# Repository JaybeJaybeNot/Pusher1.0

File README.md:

<p align="center"><i>June 8, 2026</i></p>

**Affiliation:** Fallout, Hackclub

Sanity Checked by a friend, a CS Graduate from UofM working in robotics.

Pusher is a **4 Degree of Freedom wearable robotic arm** based on the anatomical structure of the human arm, with a maximum reach of approximately **0.65 meters** and a weight of **5 kilograms**. It is designed for **modularity**, aiming to serve as an affordable, general-purpose **research platform** for Human-Computer Interfacing, such as studies involving **EMG, EEG, and Computer Vision**, to assist in the **control of supernumerary arms**. As such, this project is intended for both undergraduate researchers and hobbyists looking for an introduction to the study of HCI robotics, with potential to be used in graduate-school prototyping due to the ease of production and low cost.

***Why I Started This Project***

On the surface level, the this project may seem to simply be a project aiming to develop a supernumerary, robotic arm to assist in human tasks. However, due to the modularity and inexpensiveness of the project, it serves as an amazing platform to prototype with robot theory, from inverse kinematics to computer vision, EEG/EMG signal processing, path planning, control algorithms, etc. without burning cash on hardware. In short, due to my background as an underfunded hardware researcher, I've made the "project to enable future projects"

<h1 align="center"><u>Table of Contents</u></h1>

1. [Bill of Materials](#bill-of-materials)
2. [System Diagram](#system-diagram)
3. [Building the Project](#building-the-project)
   1. [Prerequisites](#prerequisites)
   2. [Assembling Mechanical Design](#assembling-mechanical-design)
   3. [Assembling Electrical Design](#assembling-electrical-design)
   4. [Flashing Firmware](#flashing-firmware)
4. [Author's Notes](#authors-notes)
   1. [Commentary on BOM](#commentary-on-bom)
   2. [Guide to Adding Implementations (Taking Advantage of Modularity)](#guide-to-adding-implementations-taking-advantage-of-modularity)
   3. [Future Implementations by Author](#future-implementations-by-author)

<h1 align="center"><u>Bill of Materials</u></h1>

### Electronics

| Index | LCSC # | Quantity | Value | Link |
|---|---:|---:|---:|---|
| 1 | C146170 | 2 | 1.81 | [LCSC](https://www.lcsc.com/product-detail/C146170.html) |
| 2 | C22396880 | 6 | 10.34 | [LCSC](https://www.lcsc.com/product-detail/C22396880.html) |
| 3 | C49678 | 100 | 0.84 | [LCSC](https://www.lcsc.com/product-detail/C49678.html) |
| 4 | C72487 | 20 | 0.57 | [LCSC](https://www.lcsc.com/product-detail/C72487.html) |
| 5 | C24123 | 20 | 0.30 | [LCSC](https://www.lcsc.com/product-detail/C24123.html) |
| 6 | C3869051 | 20 | 0.57 | [LCSC](https://www.lcsc.com/product-detail/C3869051.html) |
| 7 | C8465 | 5 | 0.67 | [LCSC](https://www.lcsc.com/product-detail/C8465.html) |
| 8 | C72334 | 5 | 1.01 | [LCSC](https://www.lcsc.com/product-detail/C72334.html) |
| 9 | C86513 | 4 | 6.79 | [LCSC](https://www.lcsc.com/product-detail/C86513.html) |
| 10 | C114548 | 100 | 0.36 | [LCSC](https://www.lcsc.com/product-detail/C114548.html) |
| 11 | C2930231 | 100 | 0.19 | [LCSC](https://www.lcsc.com/product-detail/C2930231.html) |
| 12 | C90964 | 5 | 3.70 | [LCSC](https://www.lcsc.com/product-detail/C90964.html) |
| 13 | C58159 | 1 | 0.38 | [LCSC](https://www.lcsc.com/product-detail/C58159.html) |
| 14 | C7467397 | 50 | 0.65 | [LCSC](https://www.lcsc.com/product-detail/C7467397.html) |
| 15 | C2930266 | 100 | 0.19 | [LCSC](https://www.lcsc.com/product-detail/C2930266.html) |
| 16 | C2907315 | 100 | 0.22 | [LCSC](https://www.lcsc.com/product-detail/C2907315.html) |
|  |  | **Total** | **28.59** |  |

### Mechanical

| Part name | Quantity | Value | Link |
|---|---:|---:|---|
| PLA Filament | 1 | 7.36 | [AliExpress](https://www.aliexpress.us/item/3256806054300015.html?spm=a2g0o.productlist.main.3.6f78379d5OwR1X&algo_pvid=498c2f52-b8c2-4add-bea6-f9bda40c924e&algo_exp_id=498c2f52-b8c2-4add-bea6-f9bda40c924e-2&pdp_ext_f=%7B%22order%22%3A%22488%22%2C%22eval%22%3A%221%22%2C%22fromPage%22%3A%22search%22%7D&pdp_npi=6%40dis%21USD%2122.79%217.36%21%21%2122.79%217.36%21%402140c1c317807875296987000e9684%2112000058209259440%21sea%21US%210%21ABX%211%210%21n_tag%3A-29910%3Bd%3Ae1bbef76%3Bm03_new_user%3A-29895%3BpisId%3A5000000208023469&curPageLogUid=Qx4M7j8exyPx&utparam-url=scene%3Asearch%7Cquery_from%3A%7Cx_object_id%3A1005006240614767%7C_p_origin_prod%3A) |
| motors | 4 | 30 | [Precision Mini Drives](https://precisionminidrives.com/product/shaft-diameter-8mm-10mm-micro-dc-gear-motor-model-nfp-42-775-ce-12v-24v?attribute_option=12V%2C+80RPM&attribute_shaft-diameter=10mm&utm_source=GoogleAds&utm_campaign=PMax&utm_medium=Google%20Shopping&utm_term=adtribes&utm_content=%7Bproduct_id%7D&gad_source=1&gad_campaignid=18478080173&gbraid=0AAAAAomY7RXK-6ddvY5v_P-wvX2-wvXLt&gclid=CjwKCAjw5NvPBhAoEiwA_2egfvITADIqACLw4gyQt7JJ5pv2qg0MlFNwTrXCpuVo1aJEWzca6XUyrBoCjcwQAvD_BwE) |
| RU-28 | 4 | 19.91 | [AliExpress](https://www.aliexpress.us/item/3256809392312866.html?src=google&src=google&albch=shopping&acnt=708-803-3821&isdl=y&slnk=&plac=&mtctp=&albbt=Google_7_shopping&aff_platform=google&aff_short_key=UneMJZVf&gclsrc=aw.ds&albagn=888888&ds_e_adid=&ds_e_matchtype=&ds_e_device=c&ds_e_network=x&ds_e_product_group_id=&ds_e_product_id=en3256809392312866&ds_e_product_merchant_id=107675220&ds_e_product_country=US&ds_e_product_language=en&ds_e_product_channel=online&ds_e_product_store_id=&ds_url_v=2&albcp=20123152476&albag=&isSmbAutoCall=false&needSmbHouyi=false&gad_source=1&gad_campaignid=20127768206&gbraid=0AAAAAD6I-hH5MzbM-Qht5WI26YJI1jQ7x&gclid=CjwKCAjw5NvPBhAoEiwA_2egfknGl0bGc7tc0ydw4pmODKzmqiRzPcj2s5EQ8m0HpaPSL7tY9xceahoCLmEQAvD_BwE&gatewayAdapt=glo2usa) |
| M5 Screws (x50) | 1 | 15 | [Amazon Japan](https://www.amazon.co.jp/-/en/Button-Socket-Screws-Finish-BHSSM5X10B-50-SL/dp/B07DZN3FP5) |
| M3 screws and nuts (x20) | 1 | 9 | [Amazon Japan](https://www.amazon.co.jp/-/en/Phillips-Machine-Washers-Plastic-Countersunk/dp/B0B9YGNKV6) |
| m5 nuts (x50) | 1 | 13 | [Amazon Japan](https://www.amazon.co.jp/-/en/Thin-Nuts-Stainless-Steel-Flat/dp/B0CQ55XWQX?th=1) |
|  |  | **Total** | **244** |

**Total project cost:** **272.59**

<h1 align="center"><u>System Diagram</u></h1>

<h1 align="center"><u>Building the Project</u></h1>

## Prerequisites

what you will need:

- A 3d printer such as Bambu Lab capable of a printing area of 
- VS Code (my goat!)
- STM32CubeIDE 
- If you have v2.0 and later versions of STM32CubeIDE, you’ll also need STM32CubeMX
- ESP32 IDF
- Cura 
- an STM32 Nucleo Board
- Soldering:

Soldering:

- Soldering iron 
- Brass wool (sponges is useable, but not recommended) 
- Flux 
- Soldering gun 
- Fume extractor 
- Solder wick (recommended to remove excess solder) 

## Assembling Mechanical Design

For assembly, please see the `FINAL ASSEMBLY` file in the `mechanical design` folder, opened in CAD software such as Fusion 360.

The material modeled for stress testing and manufacturability is PLA plastic, intended for 3D printers such as the Bambu models.

In a slicer such as Cura, print the following:

- 1x `Bicep_And_Cap`
- 1x `Bicep_RU_28_Connector` (in `Bicep_And_Cap`)
- 1x `Forearm`
- 3x `Joint_Cover`
- 1x `Joint1`
- 2x `Joints_2_and_3`
- 3x `RU_28_Connector`

Approximately ~2 kg in PLA.

To assemble the physical design, it is recommended to have 30x M5 screws (10 mm) and 30x matching nuts. Then, use 15x M3 screws (10 mm) with 15x matching nuts.

## Assembling Electrical Design

Trusted vendors such as [JLCPCB](https://jlcpcb.com/) and [LCSC](https://www.lcsc.com/).

After ordering your PCB and components from JLCPCB and LCSC, hand-solder them as follows:

- 4x motor driver PCBs

- 1x main controller PCB

Motor driver PCBs are secured in a dedicated mount, 

which is fastened to the joints themselves.

The controller PCB is left separate from the rest of the arm. The recommended option is to keep it on a desk during assembly and strap it to the arm during operation.

The wiring diagram is as follows:

- Red — 24 V and 3.3 V power supply bus
- Yellow — I2C communication bus

Connections:

- From Joint 1 to Joint 2\

- From Joint 2 to Joint 3

- From Joint 3 to Bicep

The firmware includes a 360-degree clamp to prevent wires from excessive twisting and strain.

## Flashing Firmware

### Flashing STM32F103C8T6
Note: The firmware should all be in the “Brushed_DC_Motor_Controller_STM32” folder (this is the folder you select for “create project from existing stm32cubeide project”). But for additional documentation, the pinouts and clock configuration is provided below:

In STM32cubeMX, configure the pins as follows:

Now, in the Clock tab, configure the clocks as follows:

Note: The firmware should be placed in the `Brushed_DC_Motor_Controller_STM32` folder. This is the folder you select when creating a project from an existing STM32CubeIDE project.

Step 1: Connect the SWDIO, SWCLK, GND, and 3v3 on the Motor Driver stm32 with the corresponding pins on your ST-LINK. Preferably, any STM32Nucleo can be used in order to avoid third party flashers that do not work. (trust me, speaking from experience). 

(Remove the “ST-Link isolation jumpers” on CN2 on the Nucleo Board so that you’re programming the dc motor driver, not the Nucleo itself)

Step 2: Import “Brushed_DC_Motor_Controller_STM32” as an “Existing STM32 project” into stm32cubeIDE. 

Step 3: Open the project, and find the build tool on the top toolbar, then click on it: 

Verify that there are no errors. Most build errors arise from workspace configuration. If that happens, close STM32CubeIDE first. Then, reopen. When it asks for a workspace, select the “Software” folder. It should create the corresponding metadata files. Confirm that files are there. 

Step 4: Click on “debug” tool. 

Step 5: Click on “Run”:

If flashing succeeds, STM32CubeIDE should display a successful download message in the console.

### Flashing ESP32

1. Follow the steps in the AKP's IoT Tech video to download and set up ESP32 IDF. Stop around 4:20, after creating a project folder.

YouTube video: https://www.youtube.com/watch?v=xQ-Zk0FaK-c

2. At 4:20, replace the code in `hello_world_main.c` with the contents of `main.c` located in the `ESP32 Joystick Controller` folder.
3. The code does not use external libraries, so no additional imports are needed.
4. In the ESP32-IDF terminal, type:

```bash
idf.py set-target esp32
idf.py build
```

5. Connect the ESP32 to your computer via USB.

On Windows, select the ESP32 model and the communication port. Ports usually appear as `COMx`.

Then run:

```bash
idf.py -p COM3 flash
```

Replace `3` in `COM3` with the corresponding COM number.

#### Mac

On Mac, ports usually appear as `/dev/ttyUSBx`.

You can identify the port with:

```bash
ls -la /dev | grep -E "cu\.(SLAB|usbserial)"
```

Then follow these steps:

```bash
source ~/esp/esp-idf/export.sh
idf.py set-target esp32
idf.py -p /dev/cu.SLAB_USBtoUART flash
```

#### Linux

On Linux, ports usually appear as `/dev/ttyACMx`.

First, add your user to the hardware access group:

Ubuntu/Debian:

```bash
sudo usermod -aG dialout $USER
```

Arch Linux:

```bash
sudo usermod -aG uucp $USER
```

Then, find the device path with:

```bash
ls /dev/ttyUSB* /dev/ttyACM*
```

Then navigate into your project directory and select the model:

```bash
idf.py set-target esp32
```

Finally, flash and monitor:

```bash
idf.py -p /dev/ttyUSB0 flash monitor
```

Replace `/dev/ttyUSB0` with the actual device path identified above.

<h1 align="center"><u>Author's Notes</u></h1>

## Commentary on BOM

## Guide to Adding Implementations (Taking Advantage of Modularity)

## Future Implementations by Author

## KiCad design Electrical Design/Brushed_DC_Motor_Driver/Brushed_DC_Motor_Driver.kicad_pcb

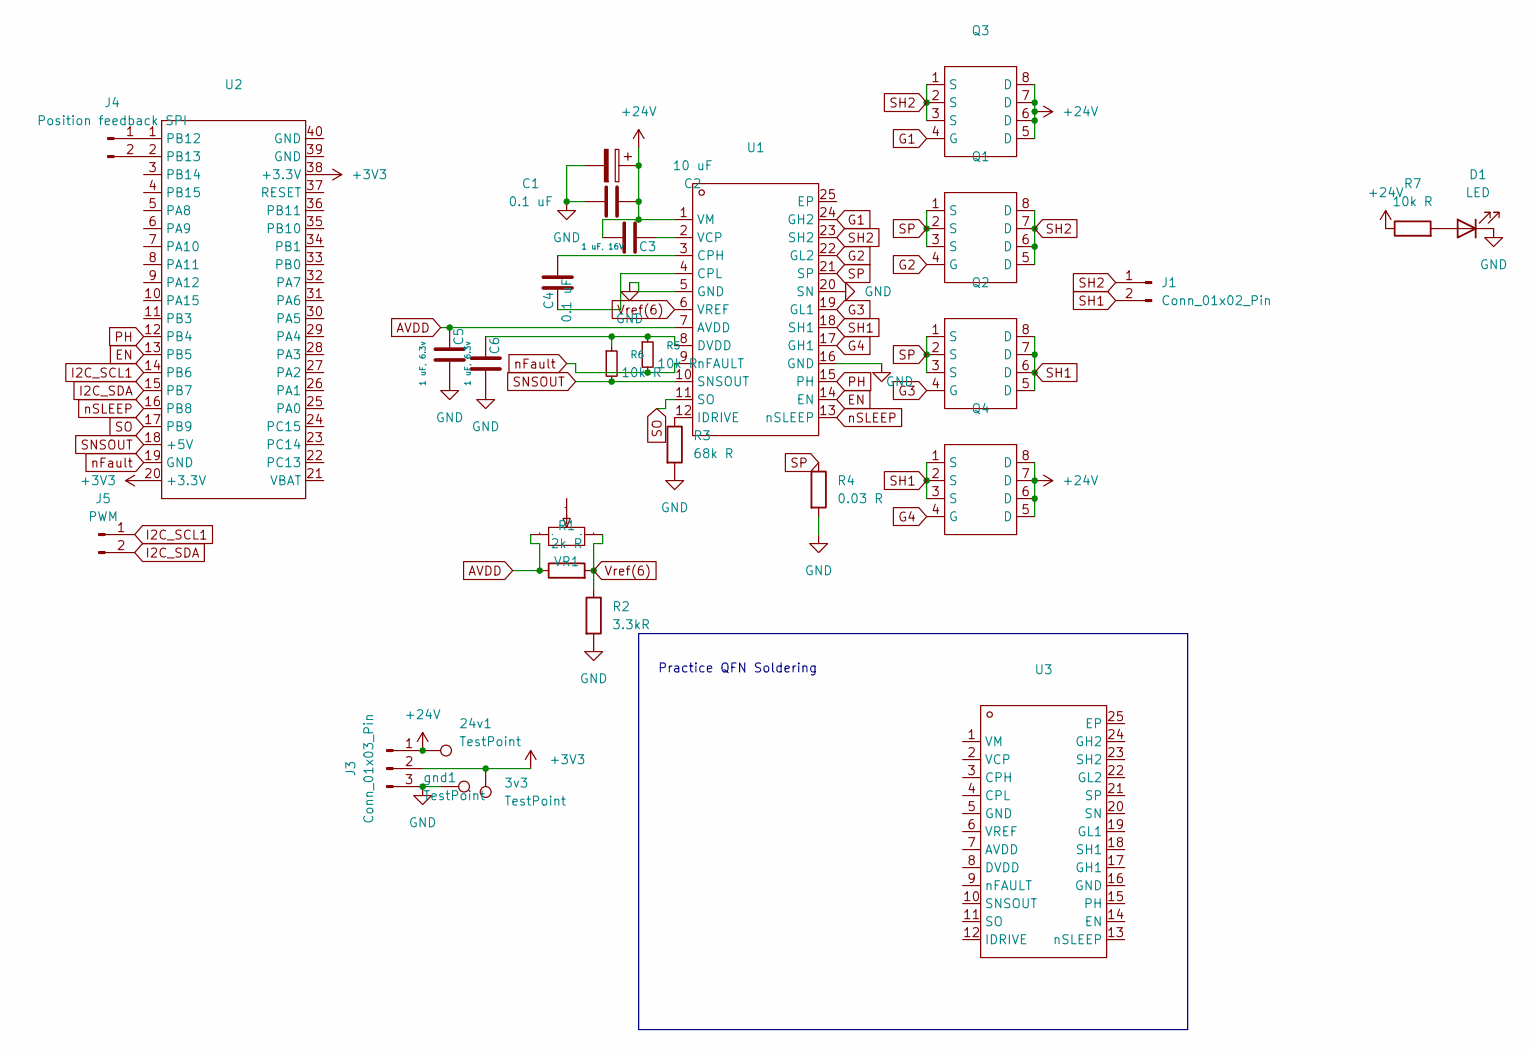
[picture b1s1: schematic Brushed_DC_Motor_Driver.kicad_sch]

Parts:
3v3, 24v1: TestPoint; TestPoint_Loop_D2.50mm_Drill1.0mm_LowProfile
C1, C4: 0.1 uF; C_0805_2012Metric_Pad1.18x1.45mm_HandSolder
C2: 10 uF; CP_Elec_5x5.4
C3: 1 uF, 16V; C_0805_2012Metric_Pad1.18x1.45mm_HandSolder
C5, C6: 1 uF, 6.3v; C_0805_2012Metric_Pad1.18x1.45mm_HandSolder
D1: LED; C_1206_3216Metric_Pad1.33x1.80mm_HandSolder
J1: Conn_01x02_Pin; Samtec_HPM-02-01-x-S_Straight_1x02_Pitch5.08mm
J3: Conn_01x03_Pin; Samtec_HPM-03-01-x-S_Straight_1x03_Pitch5.08mm
J4: Position feedback SPI; Samtec_HPM-02-01-x-S_Straight_1x02_Pitch5.08mm
J5: PWM; Samtec_HPM-02-01-x-S_Straight_1x02_Pitch5.08mm
Q1, Q2, Q3, Q4: VSON-CLIP-8_L5.0-W6.0-P1.27-BL; Manufacturer Part CSD18540Q5B; LCSC Part Name 1个N沟道 耐压:60V
R1: 2k R; C_0805_2012Metric_Pad1.18x1.45mm_HandSolder
R2: 3.3kR; C_0805_2012Metric_Pad1.18x1.45mm_HandSolder
R3: 68k R; C_0805_2012Metric_Pad1.18x1.45mm_HandSolder
R4: 0.03 R; C_0805_2012Metric_Pad1.18x1.45mm_HandSolder
R5, R6, R7: 10k R; C_0805_2012Metric_Pad1.18x1.45mm_HandSolder
U1, U3: VQFN-24_L4.0-W4.0-P0.50-BL-EP2.5; Manufacturer Part DRV8701ERGER; LCSC Part Name 有刷直流电机驱动芯片 45V
U2: CONN-TH_L53.3-W22.9_STM32F103C8T6-CARD; Manufacturer Part LCKFB-DKX-STM32F103C8T6; LCSC Part Name 立创·地阔星-STM32F103C8T6开发板
VR1: 10kΩ; RES-ADJ-TH_3362P; Manufacturer Part 3362P-1-103LF; LCSC Part Name 10kΩ ±10%
gnd1: TestPoint; TestPoint_Loop_D2.50mm_Drill1.0mm_LowProfile

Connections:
+3V3: 3v3.1, J3.2, U2.20 (+3.3V), U2.38 (+3.3V)
+24V: 24v1.1, C1.2, C2.1, C3.1, J3.1, Q3.5 (D), Q3.6 (D), Q3.7 (D), Q3.8 (D), Q4.5 (D), Q4.6 (D), Q4.7 (D), Q4.8 (D), R7.1, U1.1 (VM); also elsewhere on the board
AVDD: C5.2, R1.1, U1.7 (AVDD), VR1.3; also elsewhere on the board
EN: U1.14 (EN), U2.13 (PB5); also elsewhere on the board
G1: Q3.4 (G), U1.24 (GH2); also elsewhere on the board
G2: Q1.4 (G), U1.22 (GL2); also elsewhere on the board
G3: Q2.4 (G), U1.19 (GL1); also elsewhere on the board
G4: Q4.4 (G), U1.17 (GH1); also elsewhere on the board
GND: C1.1, C2.2, C5.1, C6.1, D1.1 (K), J3.3, R2.2, R3.2, R4.2, U1.5 (GND), U1.16 (GND), U1.20 (SN), gnd1.1; also elsewhere on the board
I2C_SCL1: J5.1, U2.14 (PB6)
I2C_SDA: J5.2, U2.15 (PB7)
unnamed: D1.2 (A), R7.2
unnamed: J4.1, U2.1 (PB12)
unnamed: J4.2, U2.2 (PB13)
unnamed 14: C4.2, U1.3 (CPH); also elsewhere on the board
unnamed 15: C4.1, U1.4 (CPL); also elsewhere on the board
unnamed 16: C6.2, R5.1, R6.1, U1.8 (DVDD); also elsewhere on the board
unnamed 17: R3.1, U1.12 (IDRIVE); also elsewhere on the board
unnamed 18: C3.2, U1.2 (VCP); also elsewhere on the board
PH: U1.15 (PH), U2.12 (PB4); also elsewhere on the board
SH1: J1.2, Q2.5 (D), Q2.6 (D), Q2.7 (D), Q2.8 (D), Q4.1 (S), Q4.2 (S), Q4.3 (S), U1.18 (SH1); also elsewhere on the board
SH2: J1.1, Q1.5 (D), Q1.6 (D), Q1.7 (D), Q1.8 (D), Q3.1 (S), Q3.2 (S), Q3.3 (S), U1.23 (SH2); also elsewhere on the board
SNSOUT: R6.2, U1.10 (SNSOUT), U2.18 (+5V); also elsewhere on the board
SO: U1.11 (SO), U2.17 (PB9); also elsewhere on the board
SP: Q1.1 (S), Q1.2 (S), Q1.3 (S), Q2.1 (S), Q2.2 (S), Q2.3 (S), R4.1, U1.21 (SP); also elsewhere on the board
Vref(6): R1.2, R2.1, U1.6 (VREF), VR1.1; also elsewhere on the board
nFault: R5.2, U1.9 (nFAULT), U2.19 (GND); also elsewhere on the board
nSLEEP: U1.13 (nSLEEP), U2.16 (PB8); also elsewhere on the board

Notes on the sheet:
Practice QFN Soldering

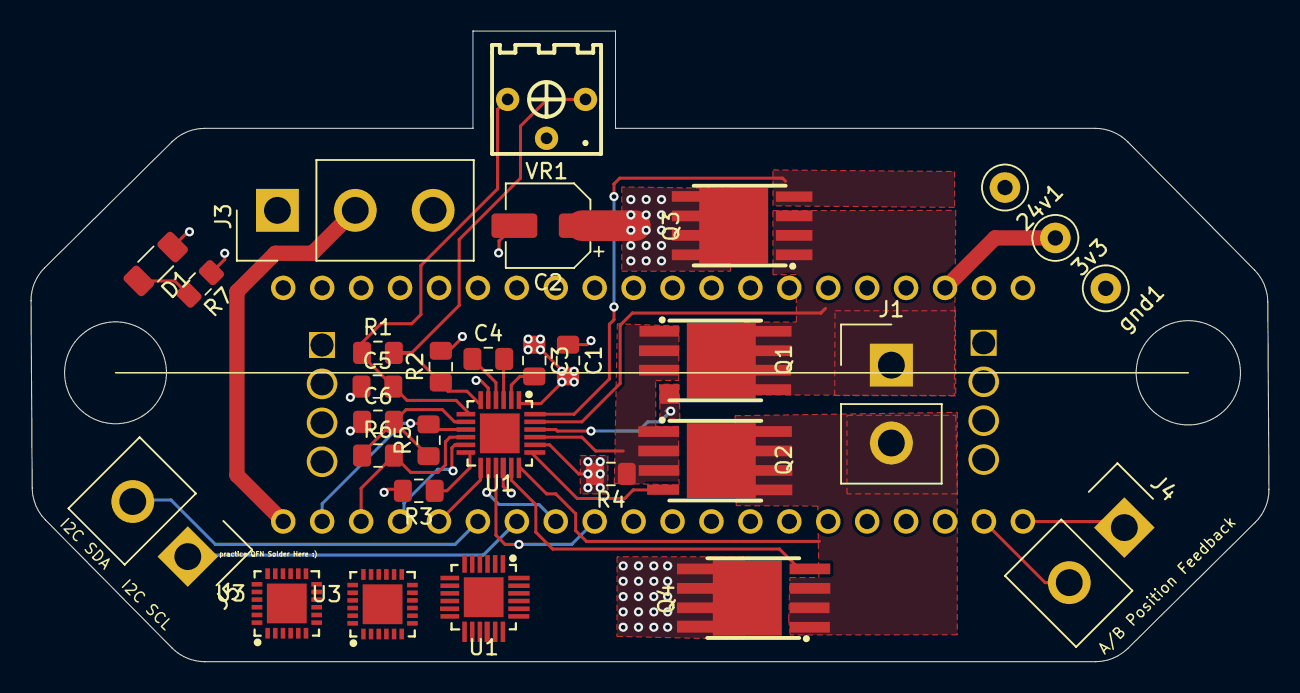
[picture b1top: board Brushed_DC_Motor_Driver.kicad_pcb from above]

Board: 4 copper layers, 80.8 x 41.2 mm, 31 parts (1 on the bottom side), 28 nets.

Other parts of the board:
U1#2, U3#2: VQFN-24_L4.0-W4.0-P0.50-BL-EP2.5

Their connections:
+24V: U1#2.1 (VM); also elsewhere on the board
AVDD: U1#2.7 (AVDD); also elsewhere on the board
EN: U1#2.14 (EN); also elsewhere on the board
G1: U1#2.24 (GH2); also elsewhere on the board
G2: U1#2.22 (GL2); also elsewhere on the board
G3: U1#2.19 (GL1); also elsewhere on the board
G4: U1#2.17 (GH1); also elsewhere on the board
GND: U1#2.5 (GND), U1#2.16 (GND), U1#2.20 (SN); also elsewhere on the board
unnamed 14: U1#2.3 (CPH); also elsewhere on the board
unnamed 15: U1#2.4 (CPL); also elsewhere on the board
unnamed 16: U1#2.8 (DVDD); also elsewhere on the board
unnamed 17: U1#2.12 (IDRIVE); also elsewhere on the board
unnamed 18: U1#2.2 (VCP); also elsewhere on the board
PH: U1#2.15 (PH); also elsewhere on the board
SH1: U1#2.18 (SH1); also elsewhere on the board
SH2: U1#2.23 (SH2); also elsewhere on the board
SNSOUT: U1#2.10 (SNSOUT); also elsewhere on the board
SO: U1#2.11 (SO); also elsewhere on the board
SP: U1#2.21 (SP); also elsewhere on the board
Vref(6): U1#2.6 (VREF); also elsewhere on the board
nFault: U1#2.9 (nFAULT); also elsewhere on the board
nSLEEP: U1#2.13 (nSLEEP); also elsewhere on the board

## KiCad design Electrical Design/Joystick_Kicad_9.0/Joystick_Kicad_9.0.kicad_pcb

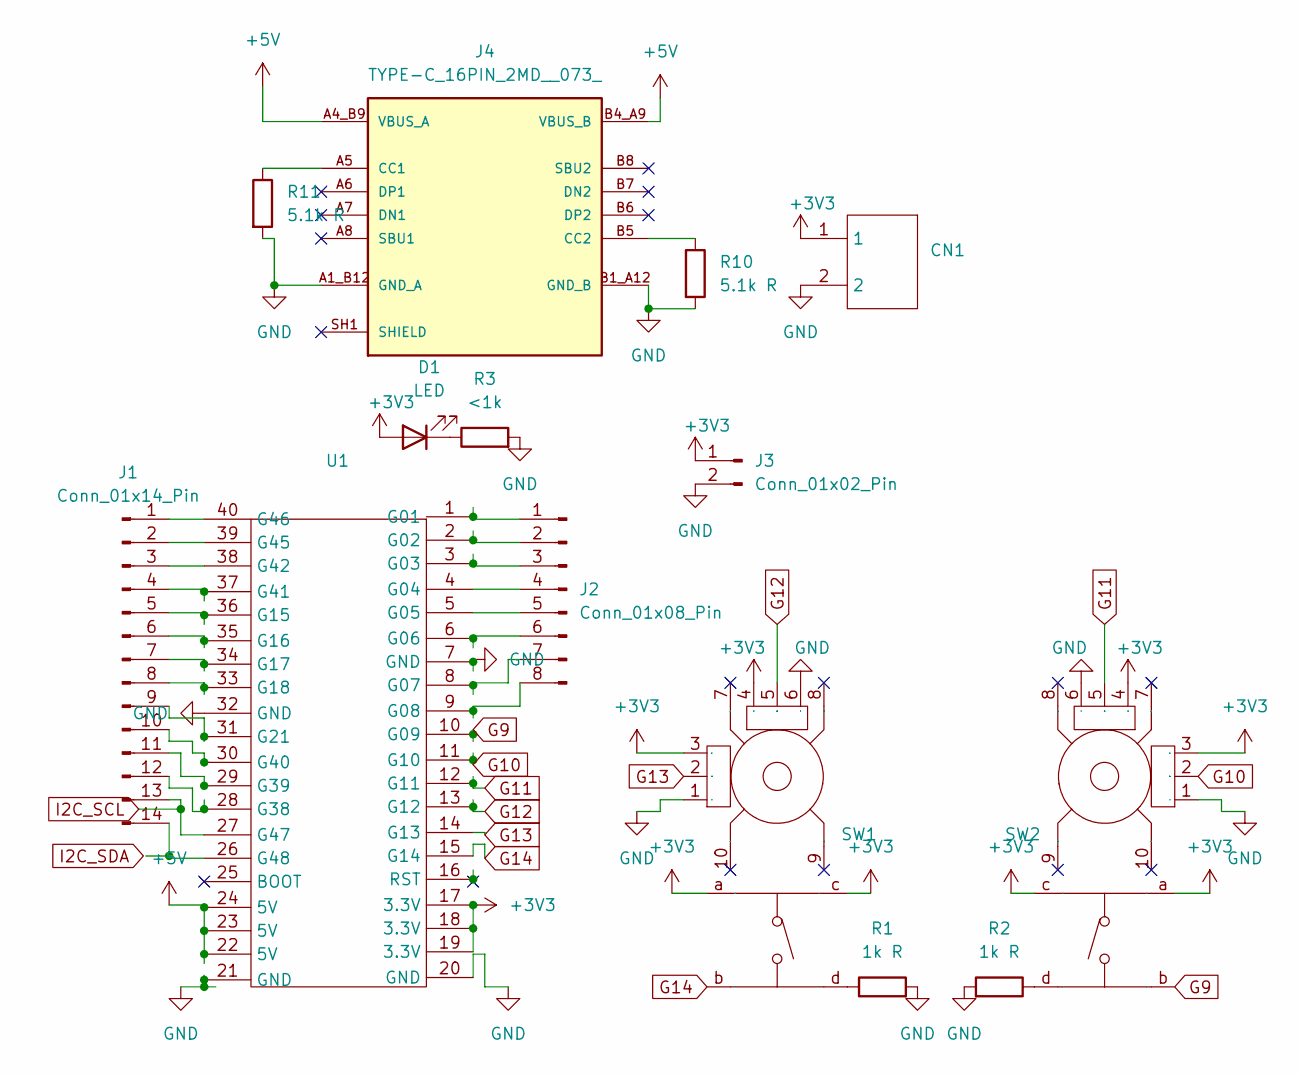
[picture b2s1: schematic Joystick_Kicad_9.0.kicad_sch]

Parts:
CN1: CONN-TH_B2B-PH-K-S; Manufacturer Part B2B-PH-K-S(LF)(SN); LCSC Part Name 1x2P 间距:2mm 直插 系列:PH
D1: LED; C_1206_3216Metric_Pad1.33x1.80mm_HandSolder
J1: Conn_01x14_Pin; Samtec_HPM-14-01-x-S_Straight_1x14_Pitch5.08mm
J2: Conn_01x08_Pin; Samtec_HPM-08-01-x-S_Straight_1x08_Pitch5.08mm
J3: Conn_01x02_Pin; Samtec_HPM-02-01-x-S_Straight_1x02_Pitch5.08mm
J4: TYPE-C_16PIN_2MD__073_; SHOUHAN_TYPE-C_16PIN_2MD__073_; PARTREV A
R1, R2: 1k R; C_1206_3216Metric_Pad1.33x1.80mm_HandSolder
R3: <1k; C_1206_3216Metric_Pad1.33x1.80mm_HandSolder
R10, R11: 5.1k R; R_1206_3216Metric_Pad1.30x1.75mm_HandSolder
SW1, SW2: SW-TH_RKJXV1224005; Manufacturer Part RKJXV1224005; LCSC Part Name RKJXV1224005
U1: DIP-40_L20.32-W51.66-P2.54-LS15.24; Manufacturer Part LCKFB-ESP32S3R8N8; LCSC Part Name 立创·ESP32S3R8N8 开发板

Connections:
+3V3: CN1.1, D1.2 (A), J3.1, SW1.3 (A), SW1.4 (A), SW1.a, SW1.c, SW2.3 (A), SW2.4 (A), SW2.a, SW2.c, U1.17 (3.3V), U1.18 (3.3V), U1.19 (3.3V)
+5V: J4.A4_B9 (VBUS_A), J4.B4_A9 (VBUS_B), U1.22 (5V), U1.23 (5V), U1.24 (5V)
G9: SW2.b, U1.10 (G09)
G10: SW2.2 (DTA), U1.11 (G10)
G11: SW2.5 (DTA), U1.12 (G11)
G12: SW1.5 (DTA), U1.13 (G12)
G13: SW1.2 (DTA), U1.14 (G13)
G14: SW1.b, U1.15 (G14)
GND: CN1.2, J3.2, J4.A1_B12 (GND_A), J4.B1_A12 (GND_B), R1.2, R2.2, R3.2, R10.2, R11.2, SW1.1 (B), SW1.6 (B), SW2.1 (B), SW2.6 (B), U1.7 (GND), U1.20 (GND), U1.21 (GND), U1.32 (GND)
unnamed: D1.1 (K), R3.1
unnamed: J1.1, U1.40 (G46)
unnamed: J1.2, U1.39 (G45)
unnamed: J1.3, U1.38 (G42)
unnamed: J1.4, U1.37 (G41)
unnamed: J1.5, U1.36 (G15)
unnamed: J1.6, U1.35 (G16)
unnamed: J1.7, U1.34 (G17)
unnamed: J1.8, U1.33 (G18)
unnamed: J1.9, U1.31 (G21)
unnamed: J1.10, U1.30 (G40)
unnamed: J1.11, U1.29 (G39)
unnamed: J1.12, U1.28 (G38)
unnamed: J1.13, U1.27 (G47)
unnamed: J1.14, U1.26 (G48)
unnamed: J2.1, U1.1 (G01)
unnamed: J2.2, U1.2 (G02)
unnamed: J2.3, U1.3 (G03)
unnamed: J2.4, U1.4 (G04)
unnamed: J2.5, U1.5 (G05)
unnamed: J2.6, U1.6 (G06)
unnamed: J2.7, U1.8 (G07)
unnamed: J2.8, U1.9 (G08)
unnamed: J4.A5 (CC1), R11.1
unnamed: J4.B5 (CC2), R10.1
unnamed: R1.1, SW1.d
unnamed: R2.1, SW2.d

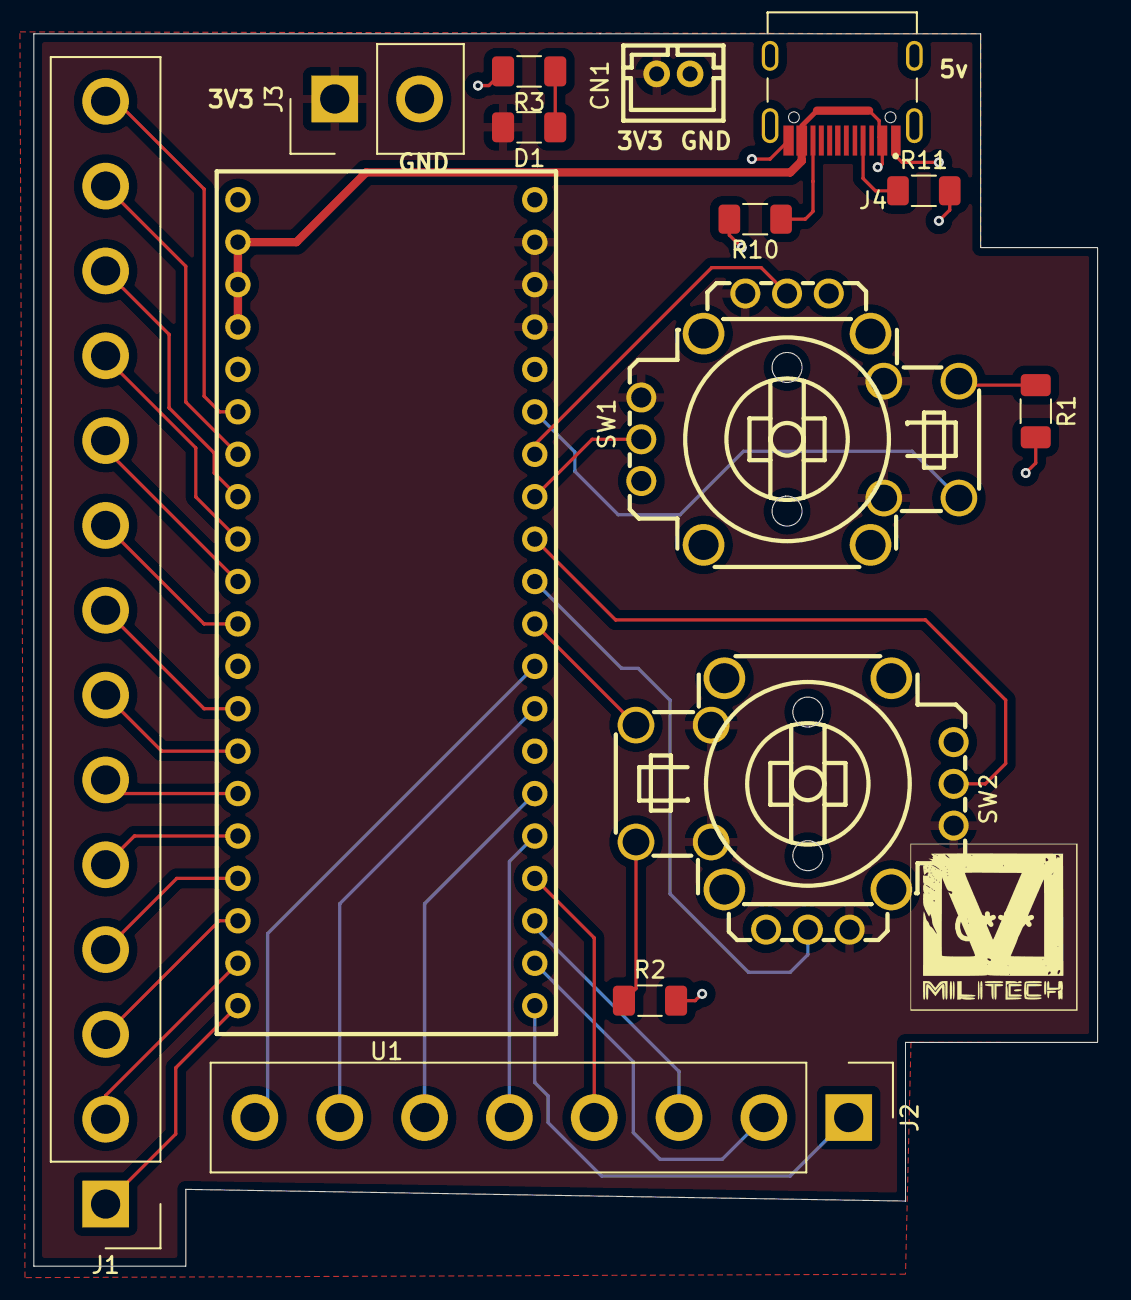
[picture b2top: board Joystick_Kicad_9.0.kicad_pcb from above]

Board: 2 copper layers, 63.7 x 73.8 mm, 14 parts (0 on the bottom side), 36 nets.

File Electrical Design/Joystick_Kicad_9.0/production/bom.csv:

Designator,Footprint,Quantity,Value,LCSC Part #
CN1,CONN-TH_B2B-PH-K-S,1,~,
D1,1206,1,LED,
J1,Samtec_HPM-14-01-x-S_Straight_1x14_Pitch5.08mm,1,Conn_01x14_Pin,
J2,Samtec_HPM-08-01-x-S_Straight_1x08_Pitch5.08mm,1,Conn_01x08_Pin,
J3,Samtec_HPM-02-01-x-S_Straight_1x02_Pitch5.08mm,1,Conn_01x02_Pin,
J4,SHOUHAN_TYPE-C_16PIN_2MD__073_,1,TYPE-C_16PIN_2MD__073_,
"R1, R2",1206,2,R,
"R10, R11",1206,2,5.1k R,
R3,1206,1,<1k,
"SW1, SW2",SW-TH_RKJXV1224005,2,~,
U1,DIP-40_L20.32-W51.66-P2.54-LS15.24,1,~,

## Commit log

2026-06-07 Added BOM
2026-06-07 Added STM32 code for brushed DC Motor
2026-06-08 added esp32 IDF firmware
2026-06-08 updated BOM #1
2026-06-08 updated BOM #2
2026-06-12 Revert "updated Readme"
    This reverts commit 388981b10109a82fa148f99a4a2ef8b91c29792a.
2026-06-12 added images
2026-06-13 added Zine
2026-06-13 added zine pdf
2026-06-13 Update README.md to add motivation
2026-06-18 Update README.md added project purpose statement
